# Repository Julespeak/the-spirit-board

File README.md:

# The S.P.I.R.I.T. Board

An open-source Furby controller based on the ESP32-C6 module.

The goal of this project was to create a modern interface for the original 1998 Furby so that it could be reprogammed into a "haunted" version of the orignal toy. 👻

### Special Peripheral Interface for Receiving Internet Transmissions
The design of the board is based closely on the [Adafruit ESP32-C6 Feather](https://learn.adafruit.com/adafruit-esp32-c6-feather).

### Using the project
The project was designed using KiCAD. It is fully portable. You should be able to clone the repo and open the .pro file with the latest version of KiCAD.

The version of KiCAD used in the design was 9.0. If you use something else, YMMV.

### Data Analysis Environment

This project includes a Jupyter Lab environment for analyzing data from the Spirit Board (e.g., RTS timing data, signal analysis). The environment is managed using `uv`, a fast Python package manager.

**Prerequisites:**
- Python 3.10 or higher
- `uv` package manager - Install with: `curl -LsSf https://astral.sh/uv/install.sh | sh`

**Setup:**
1. Install dependencies and create virtual environment:
   ```bash
   uv sync
   ```

2. Launch Jupyter Lab:
   ```bash
   uv run jupyter lab
   ```

3. Open notebooks in the `notebooks/` directory

**Adding Dependencies:**
To add new packages for data analysis:
```bash
uv add pandas           # Data analysis
uv add scikit-learn     # Machine learning
uv add seaborn          # Statistical visualization
```

**Note:** Always commit both `pyproject.toml` and `uv.lock` to ensure reproducible environments across different machines.

### Adding new components to the library
1) Download the part footprint/3D model archive from Mouser
2) Copy the .kicad_mod file to the lib folder
3) Edit the .kicad_mod fle to include 'lib/the-spirit-board.3dshapes/' in the file name of the step file
4) Copy the step file into the 3D lib/<>.3dshapes folder
5) Insert the contents of the .kicad_sym file into the master .kicad_sym file
6) Save everything and commit

### Documentation

- **[Furby Soundcard Protocol Specification](docs/soundcard_spec.md)** - Complete technical specification of the Furby sound coprocessor communication protocol
- **[CLAUDE.md](CLAUDE.md)** - AI assistant context and project structure
- **[firmware/invoker/README.md](firmware/invoker/README.md)** - Firmware module documentation

### Useful links and sources
- [Technical information](https://official-furby.fandom.com/wiki/Furby_(1998)/Technical_information) on the original 1998 Furby from the offical fan wiki
- Reversed-engineered 1998 Furby [schematic](https://cdn.preterhuman.net/texts/engineering/Furby,%20Reverse-Engineered.pdf)
- I got inspiration for the I2S microphone peripheral from the [onju-voice](https://github.com/justLV/onju-voice) project
- This [Instructable](https://www.instructables.com/Control-a-Furby-with-Arduino-or-other-microcontrol/) on how to use an Arduino to control a Furby was quite useful, particularly with the labeled board photos
  - There are also lots of useful details on getting to the PCB in the previous [Instructable](https://www.instructables.com/Furby-Brain-Surgery/)
- The [original patent](https://patentimages.storage.googleapis.com/82/75/e2/13a4a9268abff4/US6544098.pdf) for the Furby is incredibly detailed—and fascinating!
- Useful [photo](https://sundbergferar.com/wp-content/uploads/2022/08/Furby.product.teardown.sundbergferar5.jpg) of the front side of the main PCB inside the Furby; the processor board that the S.P.I.R.I.T. board replaces is on the left side of the picture
- [Technical reference manual](https://www.espressif.com/sites/default/files/documentation/esp32-c6_technical_reference_manual_en.pdf) for the ESP32-C6
- [Datasheet](https://documentation.espressif.com/esp32-c6_datasheet_en.pdf) for the ESP32-C6
- [Schematic](https://cdn-learn.adafruit.com/assets/assets/000/131/884/original/adafruit_products_schem.png?1723750406) for the Adafruit ESP32-C6 Feather

### Board photos
#### Front

#### Back

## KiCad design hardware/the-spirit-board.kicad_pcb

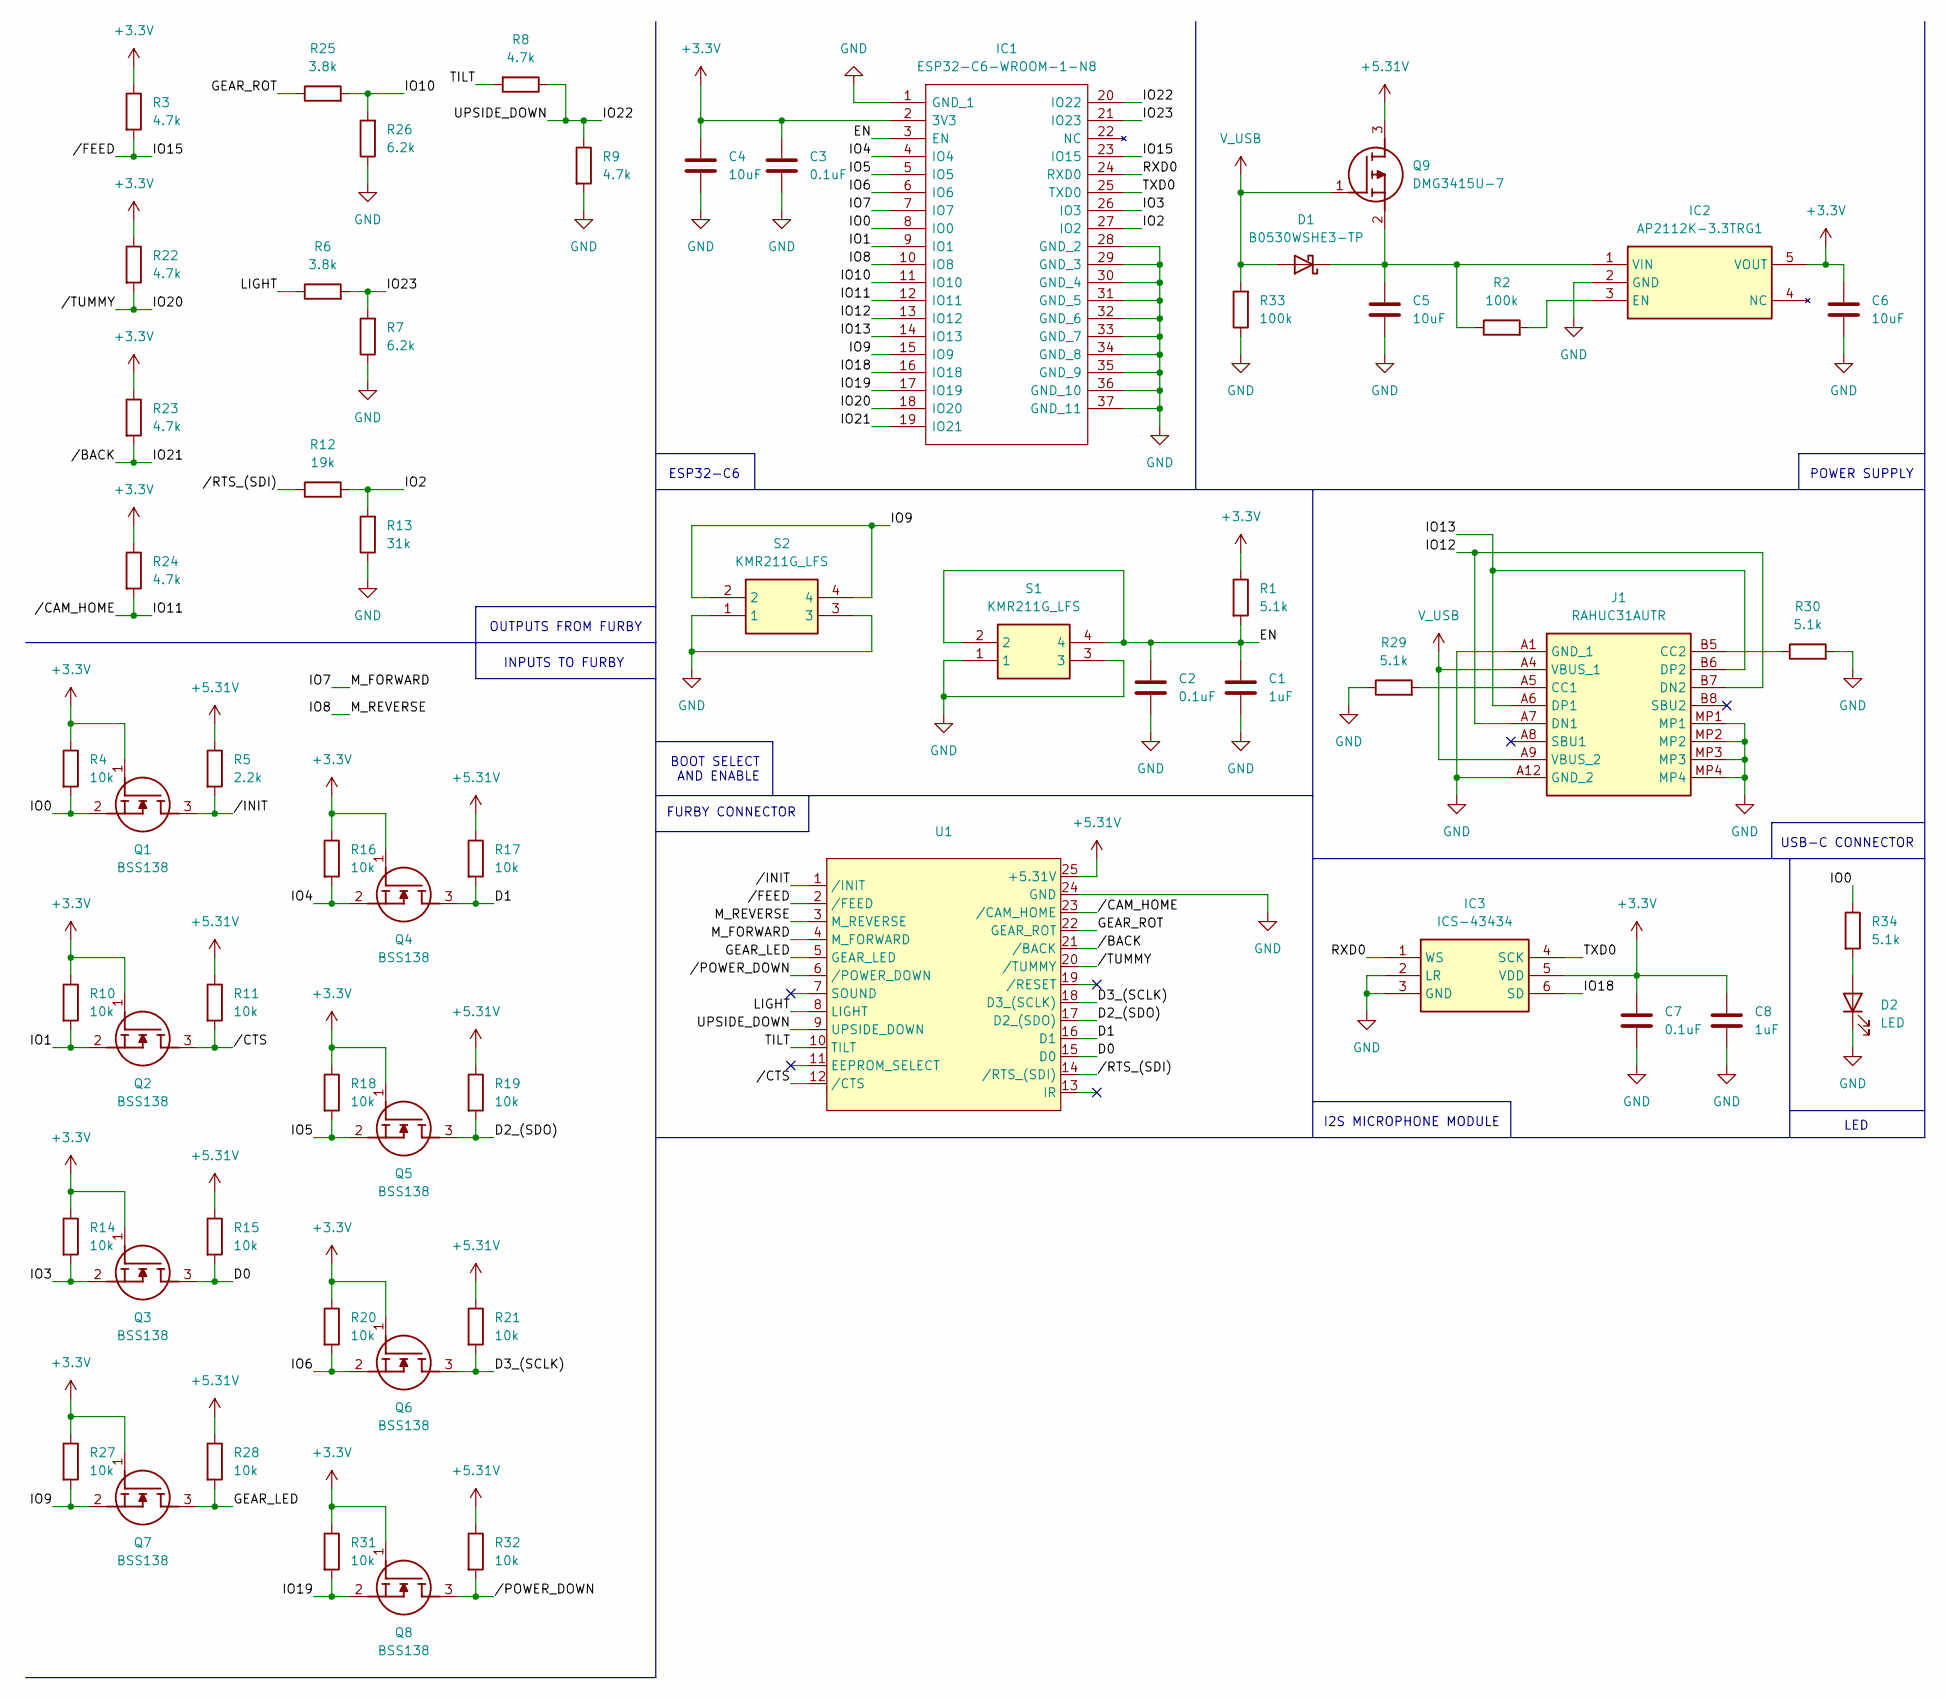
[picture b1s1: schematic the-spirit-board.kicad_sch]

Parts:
C1, C8: 1uF; C_0603_1608Metric; JLCPCB Part Number C15849
C2, C3: 0.1uF; C_0402_1005Metric; JLCPCB Part Number C307331
C4, C5, C6: 10uF; C_0805_2012Metric; JLCPCB Part Number C440198
C7: 0.1uF; C_0603_1608Metric; JLCPCB Part Number C14663
D1: B0530WSHE3-TP; D_SOD-323; JLCPCB Part Number C3759178
D2: LED; LED_0603_1608Metric; JLCPCB Part Number C2286
IC1: ESP32-C6-WROOM-1-N8; ESP32C6WROOM1N8; Mouser Part Number 356-ESP32C6WROOM1N8
IC2: AP2112K-3.3TRG1; SOT95P285X140-5N; Mouser Part Number 621-AP2112K-3.3TRG1
IC3: ICS-43434; ICS43434; Mouser Part Number 410-ICS-43434
J1: RAHUC31AUTR; Manufacturer_Part_Number RAHUC31AUTR; JLCPCB Part Number C21350227
Q1, Q2, Q3, Q4, Q5, Q6, Q7, Q8: BSS138; SOT95P240X120-3N; Mouser Part Number 512-BSS138
Q9: DMG3415U-7; SOT96P240X110-3N; Mouser Part Number 621-DMG3415U-7
R1, R29, R30, R34: 5.1k; R_0603_1608Metric; JLCPCB Part Number C23186
R2, R33: 100k; R_0603_1608Metric; JLCPCB Part Number C25803
R3, R8, R9, R22, R23, R24: 4.7k; R_0603_1608Metric; JLCPCB Part Number C23162
R4, R10, R11, R14, R15, R16, R17, R18, R19, R20, R21, R27, R28, R31, R32: 10k; R_0603_1608Metric; JLCPCB Part Number C25804
R5: 2.2k; R_0603_1608Metric; JLCPCB Part Number C4190
R6, R25: 3.8k; R_0603_1608Metric; JLCPCB Part Number C23018
R7, R26: 6.2k; R_0603_1608Metric; JLCPCB Part Number C4260
R12: 19k; R_0603_1608Metric; JLCPCB Part Number C25810
R13: 31k; R_0603_1608Metric; JLCPCB Part Number C22984
S1, S2: KMR211G_LFS; KMR_2; Mouser Part Number 611-KMR211G-LFS
U1: FURBY; JLCPCB Part Number N/A

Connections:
+3.3V: C3.1, C4.1, C6.2, C7.2, C8.2, IC1.2 (3V3), IC2.5 (VOUT), IC3.5 (VDD), Q1.1 (G), Q2.1 (G), Q3.1 (G), Q4.1 (G), Q5.1 (G), Q6.1 (G), Q7.1 (G), Q8.1 (G), R1.1, R3.1, R4.1, R10.1, R14.1, R16.1, R18.1, R20.1, R22.1, R23.1, R24.1, R27.1, R31.1
+5.31V: Q9.3 (D), R5.1, R11.1, R15.1, R17.1, R19.1, R21.1, R28.1, R32.1, U1.25 (+5.31V)
/D0: Q3.3 (D), R15.2, U1.15 (D0)
/D1: Q4.3 (D), R17.2, U1.16 (D1)
/D2_(SDO): Q5.3 (D), R19.2, U1.17 (D2_(SDO))
/D3_(SCLK): Q6.3 (D), R21.2, U1.18 (D3_(SCLK))
/EN: C1.1, C2.1, IC1.3 (EN), R1.2, S1.2, S1.4
/GEAR_LED: Q7.3 (D), R28.2, U1.5 (GEAR_LED)
/GEAR_ROT: R25.1, U1.22 (GEAR_ROT)
/IO0: IC1.8 (IO0), Q1.2 (S), R4.2, R34.1
/IO1: IC1.9 (IO1), Q2.2 (S), R10.2
/IO2: IC1.27 (IO2), R12.2, R13.2
/IO3: IC1.26 (IO3), Q3.2 (S), R14.2
/IO4: IC1.4 (IO4), Q4.2 (S), R16.2
/IO5: IC1.5 (IO5), Q5.2 (S), R18.2
/IO6: IC1.6 (IO6), Q6.2 (S), R20.2
/IO7: IC1.7 (IO7), U1.4 (M_FORWARD)
/IO8: IC1.10 (IO8), U1.3 (M_REVERSE)
/IO9: IC1.15 (IO9), Q7.2 (S), R27.2, S2.2, S2.4
/IO10: IC1.11 (IO10), R25.2, R26.2
/IO11: IC1.12 (IO11), R24.2, U1.23 (/CAM_HOME)
/IO12: IC1.13 (IO12), J1.A7 (DN1), J1.B7 (DN2)
/IO13: IC1.14 (IO13), J1.A6 (DP1), J1.B6 (DP2)
/IO15: IC1.23 (IO15), R3.2, U1.2 (/FEED)
/IO18: IC1.16 (IO18), IC3.6 (SD)
/IO19: IC1.17 (IO19), Q8.2 (S), R31.2
/IO20: IC1.18 (IO20), R22.2, U1.20 (/TUMMY)
/IO21: IC1.19 (IO21), R23.2, U1.21 (/BACK)
/IO22: IC1.20 (IO22), R8.1, R9.1, U1.9 (UPSIDE_DOWN)
/IO23: IC1.21 (IO23), R6.2, R7.2
/LIGHT: R6.1, U1.8 (LIGHT)
/RXD0: IC1.24 (RXD0), IC3.1 (WS)
/TILT: R8.2, U1.10 (TILT)
/TXD0: IC1.25 (TXD0), IC3.4 (SCK)
//CTS: Q2.3 (D), R11.2, U1.12 (/CTS)
//INIT: Q1.3 (D), R5.2, U1.1 (/INIT)
//POWER_DOWN: Q8.3 (D), R32.2, U1.6 (/POWER_DOWN)
//RTS_(SDI): R12.1, U1.14 (/RTS_(SDI))
GND: C1.2, C2.2, C3.2, C4.2, C5.1, C6.1, C7.1, C8.1, D2.1 (K), IC1.1 (GND_1), IC1.28 (GND_2), IC1.29 (GND_3), IC1.30 (GND_4), IC1.31 (GND_5), IC1.32 (GND_6), IC1.33 (GND_7), IC1.34 (GND_8), IC1.35 (GND_9), IC1.36 (GND_10), IC1.37 (GND_11), IC2.2 (GND), IC3.2 (LR), IC3.3 (GND), J1.A1 (GND_1), J1.A12 (GND_2), J1.MP1, J1.MP2, J1.MP3, J1.MP4, R7.1, R9.2, R13.1, R26.1, R29.1, R30.2, R33.1, S1.1, S1.3, S2.1, S2.3, U1.24 (GND)
unnamed: C5.2, D1.1 (K), IC2.1 (VIN), Q9.2 (S), R2.1
unnamed: D2.2 (A), R34.2
unnamed: IC2.3 (EN), R2.2
unnamed: J1.A5 (CC1), R29.2
unnamed: J1.B5 (CC2), R30.1
V_USB: D1.2 (A), J1.A4 (VBUS_1), J1.A9 (VBUS_2), Q9.1 (G), R33.2

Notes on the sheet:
I2S MICROPHONE MODULE
FURBY CONNECTOR
POWER SUPPLY
LED
INPUTS TO FURBY
BOOT SELECT AND ENABLE
ESP32-C6
USB-C CONNECTOR
OUTPUTS FROM FURBY

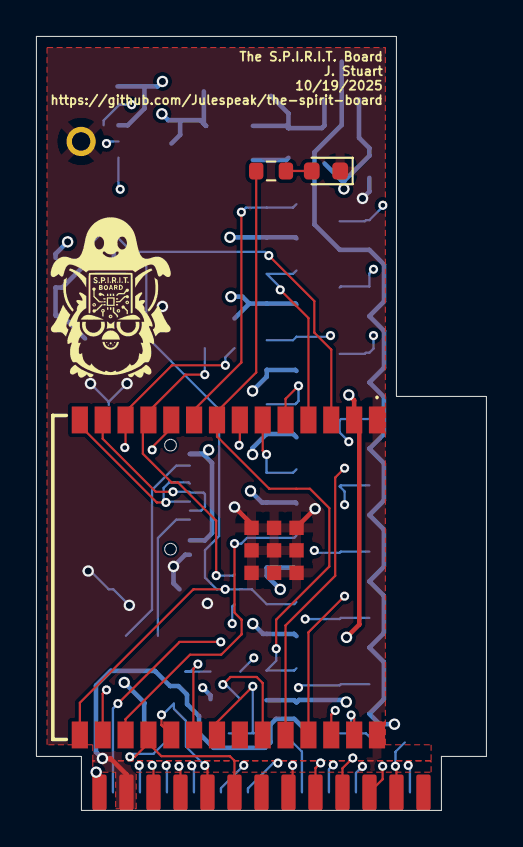
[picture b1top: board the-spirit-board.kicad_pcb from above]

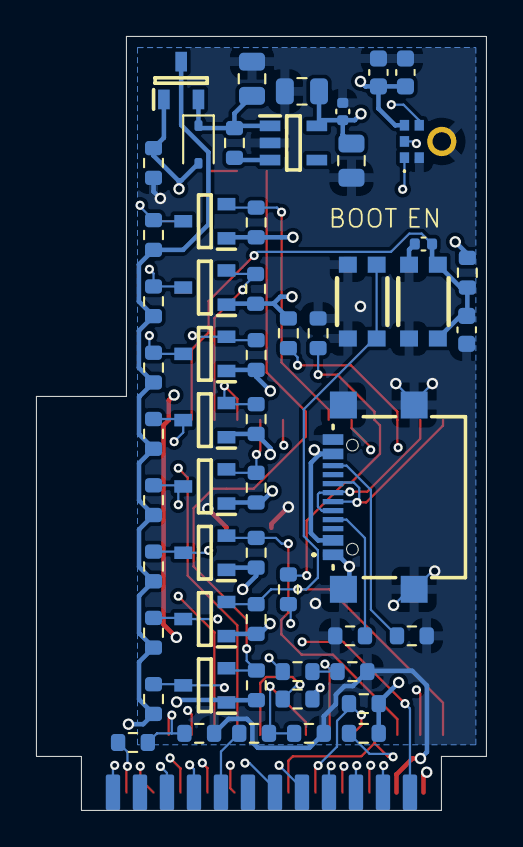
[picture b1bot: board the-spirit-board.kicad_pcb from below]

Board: 4 copper layers, 25.0 x 43.0 mm, 60 parts (56 on the bottom side), 45 nets.

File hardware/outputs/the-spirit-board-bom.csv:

Comment,Designator,Footprint,LCSC Part Number
1uF,"C1,C8",Capacitor_SMD:C_0603_1608Metric,C15849
0.1uF,"C2,C3",Capacitor_SMD:C_0402_1005Metric,C307331
10uF,"C4,C5,C6",Capacitor_SMD:C_0805_2012Metric,C440198
0.1uF,C7,Capacitor_SMD:C_0603_1608Metric,C14663
B0530WSHE3-TP,D1,Diode_SMD:D_SOD-323,C3759178
LED,D2,LED_SMD:LED_0603_1608Metric,C2286
ESP32-C6-WROOM-1-N8,IC1,TheSPIRITBoard:ESP32C6WROOM1N8,C5366877
AP2112K-3.3TRG1,IC2,TheSPIRITBoard:SOT95P285X140-5N,C51118
ICS-43434,IC3,TheSPIRITBoard:ICS43434,C5656610
RAHUC31AUTR,J1,TheSPIRITBoard:RAHUC31AUTR,C21350227
BSS138,"Q1,Q2,Q3,Q4,Q5,Q6,Q7,Q8",TheSPIRITBoard:SOT95P240X120-3N,C52895
DMG3415U-7,Q9,TheSPIRITBoard:SOT96P240X110-3N,C96616
5.1k,"R1,R29,R30,R34",Resistor_SMD:R_0603_1608Metric,C23186
100k,"R2,R33",Resistor_SMD:R_0603_1608Metric,C25803
4.7k,"R3,R8,R9,R22,R23,R24",Resistor_SMD:R_0603_1608Metric,C23162
10k,"R4,R10,R11,R14,R15,R16,R17,R18,R19,R20,R21,R27,R28,R31,R32",Resistor_SMD:R_0603_1608Metric,C25804
2.2k,R5,Resistor_SMD:R_0603_1608Metric,C4190
3.8k,"R6,R25",Resistor_SMD:R_0603_1608Metric,C23018
6.2k,"R7,R26",Resistor_SMD:R_0603_1608Metric,C4260
19k,R12,Resistor_SMD:R_0603_1608Metric,C25810
31k,R13,Resistor_SMD:R_0603_1608Metric,C22984
KMR211G_LFS,"S1,S2",TheSPIRITBoard:KMR_2,C221675

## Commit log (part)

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2025-05-17 Add project-specific libraries
2025-05-17 Add .gitignore
2025-05-18 Fix a filetype issue due to new KiCAD version
2025-06-14 Initial commit of the schematic and board files with the ESP32
2025-08-16 Add power supply and momentary switch for enable
2025-08-16 Add the footprint for the Furby and do initial connections
2025-08-16 Update .gitignore to remove .bak files
2025-09-16 Update the schematic symbol for the Furby main board connection
2025-09-16 Add the BSS138 to the component library
2025-09-17 Completed connection between the Furby and the ESP32-C6
2025-09-24 Add USB-C connection
2025-09-27 Add an I2S microphone module
2025-09-27 Initial draft of the schematic complete
2025-10-09 Update the size of the board based on new measurements of the Furby chassis
2025-10-09 Update the USB connector 3D model
2025-10-09 Update the keepout area on the ESP footprint
2025-10-09 Lots of updates to the PCB; all connections made except for one diode; working on passing DRC; targeting 4pcb
2025-10-09 Add PDF of the schematic
2025-10-19 Update the diode in the power supply
2025-10-20 Update the schematic and layout after choosing parts
2025-10-20 First take at gerber outputs
2025-10-21 Update gerbers, BOM, and placement for JLCPCB
2025-10-21 Update the placement file to a single file for top and bottom
2025-10-26 Update shematic
2025-10-26 Add datasheets
2025-10-26 Add board images
2025-10-26 Create LICENSE
2025-12-08 Split the repo into hardware and firmware; initial commit of the invoker firmware
2025-12-08 Add a firmware update to record the /RTS high duration after a nibble is sent; add a control byte for reading these data back out
2025-12-26 Update RTS timing tracking; update init sequence
2025-12-28 Add some new debug sequences, re-tool the sendNibble function to have the correct RTS/CTS handshake, fix a pullup issue with RTS
2025-12-29 Some simple whitespace changes
2026-01-01 Extend the length of the nibble list payload
2026-01-01 Add Claude to the project along with all context files; add jupyter notebooks and refactor into a library for interacting with the spirit board
2026-01-03 Updates to claude and documentation
2026-01-03 Use Claude to implement management of jupyter lab environment using uv
2026-01-06 Update the firmware to include some additional delays to try and fix a presumed timing issue; these updates did not improve comms but are good practice
2026-01-06 add a sequence for the initial phrase
2026-01-10 Remove some legacy RTS timing
2026-01-18 Big commit with the whole rebase to PlatformIO
2026-01-20 Implement network resilience
2026-01-20 Add RGB LED control to the Feather target
2026-01-21 Add audio data capture and playback to the Feather target
2026-01-21 Reduce the audio sample length to save RAM
2026-02-01 Add the audio capture to the main spirit firmware; update notebooks; implement PlatformIO workflow for spirit board
2026-02-02 Remove unnecessary agents
